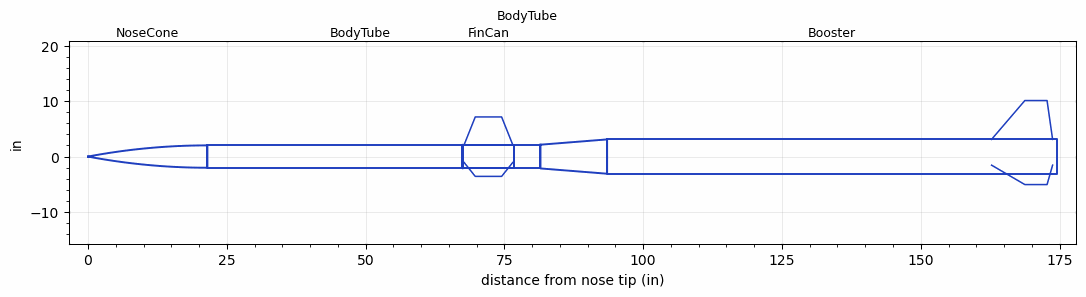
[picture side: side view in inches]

<RASAeroDocument>
 <FileVersion>2</FileVersion>
 <RocketDesign>
  <NoseCone>
   <Length>21.5</Length>
   <Diameter>4.026</Diameter>
   <Shape>Tangent Ogive</Shape>
   <BluntRadius>0.125</BluntRadius>
   <Location>0</Location>
  </NoseCone>
  <BodyTube>
   <Length>55.25</Length>
   <Diameter>4.026</Diameter>
   <Location>21.5</Location>
  </BodyTube>
  <FinCan>
   <Length>9.25</Length>
   <Diameter>4.276</Diameter>
   <InsideDiameter>4.026</InsideDiameter>
   <Location>76.75</Location>
   <ShoulderLength>0.125</ShoulderLength>
   <Offset>-9.25</Offset>
   <Fin>
    <Count>3</Count>
    <Chord>8.75</Chord>
    <Span>5</Span>
    <SweepDistance>2</SweepDistance>
    <TipChord>4.75</TipChord>
    <Thickness>0.125</Thickness>
    <LERadius>0.0625</LERadius>
    <Location>9</Location>
    <AirfoilSection>Hexagonal</AirfoilSection>
    <FX1>0.5</FX1>
    <FX3>0.5</FX3>
   </Fin>
  </FinCan>
  <BodyTube>
   <Length>4.75</Length>
   <Diameter>4.276</Diameter>
   <Location>76.75</Location>
  </BodyTube>
  <Booster>
   <Length>81</Length>
   <Diameter>6.18</Diameter>
   <InsideDiameter>4.276</InsideDiameter>
   <RailGuideDiameter>1.25</RailGuideDiameter>
   <RailGuideHeight>1</RailGuideHeight>
   <Location>81.5</Location>
   <ShoulderLength>12</ShoulderLength>
   <Fin>
    <Count>3</Count>
    <Chord>11</Chord>
    <Span>7</Span>
    <SweepDistance>6</SweepDistance>
    <TipChord>4</TipChord>
    <Thickness>0.125</Thickness>
    <LERadius>0.0625</LERadius>
    <Location>11.75</Location>
    <AirfoilSection>Hexagonal</AirfoilSection>
    <FX1>0.5</FX1>
    <FX3>0.5</FX3>
   </Fin>
  </Booster>
  <Surface>Rough Camouflage Paint</Surface>
  <ModifiedBarrowman>True</ModifiedBarrowman>
  <Turbulence>True</Turbulence>
  <UseBooster1>False</UseBooster1>
  <UseBooster2>False</UseBooster2>
 </RocketDesign>
 <LaunchSite>
  <Altitude>3500</Altitude>
  <Pressure>0</Pressure>
  <RodAngle>1</RodAngle>
  <RodLength>18</RodLength>
  <Temperature>80</Temperature>
  <WindSpeed>2</WindSpeed>
 </LaunchSite>
 <Recovery>
  <Altitude1>1000</Altitude1>
  <Altitude2>1000</Altitude2>
  <DeviceType1>None</DeviceType1>
  <DeviceType2>None</DeviceType2>
  <Event1>False</Event1>
  <Event2>False</Event2>
  <Size1>1</Size1>
  <Size2>1</Size2>
  <EventType1>None</EventType1>
  <EventType2>None</EventType2>
  <CD1>1.33</CD1>
  <CD2>1.33</CD2>
 </Recovery>
 <SimulationList>
  <Simulation>
   <SustainerEngine>K735-SK-P  (CTI)</SustainerEngine>
   <SustainerLaunchWt>26.5</SustainerLaunchWt>
   <SustainerNozzleDiameter>2.75</SustainerNozzleDiameter>
   <SustainerCG>55</SustainerCG>
   <SustainerIgnitionDelay>2</SustainerIgnitionDelay>
   <Booster1Engine>M3400-WT  (CTI)</Booster1Engine>
   <Booster1LaunchWt>83</Booster1LaunchWt>
   <Booster1SeparationDelay>0.5</Booster1SeparationDelay>
   <Booster1IgnitionDelay>0</Booster1IgnitionDelay>
   <Booster1CG>110</Booster1CG>
   <Booster1NozzleDiameter>3.625</Booster1NozzleDiameter>
   <IncludeBooster1>True</IncludeBooster1>
   <Booster2Delay>0</Booster2Delay>
   <IncludeBooster2>True</IncludeBooster2>
   <TimetoApogee>32.35056</TimetoApogee>
   <MaxAltitude>16364.87</MaxAltitude>
   <MaxVelocity>1095.519</MaxVelocity>
  </Simulation>
  <Simulation>
   <SustainerEngine>K735-SK-P  (CTI)</SustainerEngine>
   <SustainerLaunchWt>26.5</SustainerLaunchWt>
   <SustainerNozzleDiameter>2.75</SustainerNozzleDiameter>
   <SustainerCG>55</SustainerCG>
   <SustainerIgnitionDelay>2</SustainerIgnitionDelay>
   <Booster1Engine>M2505  (CTI)</Booster1Engine>
   <Booster1LaunchWt>79</Booster1LaunchWt>
   <Booster1SeparationDelay>0.5</Booster1SeparationDelay>
   <Booster1IgnitionDelay>0</Booster1IgnitionDelay>
   <Booster1CG>108</Booster1CG>
   <Booster1NozzleDiameter>3.625</Booster1NozzleDiameter>
   <IncludeBooster1>True</IncludeBooster1>
   <Booster2Delay>0</Booster2Delay>
   <IncludeBooster2>False</IncludeBooster2>
   <TimetoApogee>30.52052</TimetoApogee>
   <MaxAltitude>13441.91</MaxAltitude>
   <MaxVelocity>960.9597</MaxVelocity>
  </Simulation>
  <Simulation>
   <SustainerEngine>K510  (CTI)</SustainerEngine>
   <SustainerLaunchWt>26.5</SustainerLaunchWt>
   <SustainerNozzleDiameter>2.75</SustainerNozzleDiameter>
   <SustainerCG>55</SustainerCG>
   <SustainerIgnitionDelay>2</SustainerIgnitionDelay>
   <Booster1Engine>M2505  (CTI)</Booster1Engine>
   <Booster1LaunchWt>79</Booster1LaunchWt>
   <Booster1SeparationDelay>0.5</Booster1SeparationDelay>
   <Booster1IgnitionDelay>0</Booster1IgnitionDelay>
   <Booster1CG>108</Booster1CG>
   <Booster1NozzleDiameter>3.625</Booster1NozzleDiameter>
   <IncludeBooster1>True</IncludeBooster1>
   <Booster2Delay>0</Booster2Delay>
   <IncludeBooster2>False</IncludeBooster2>
   <TimetoApogee>33.8906</TimetoApogee>
   <MaxAltitude>16404.34</MaxAltitude>
   <MaxVelocity>1028.177</MaxVelocity>
  </Simulation>
  <Simulation>
   <SustainerEngine>K510  (CTI)</SustainerEngine>
   <SustainerLaunchWt>26.5</SustainerLaunchWt>
   <SustainerNozzleDiameter>2.75</SustainerNozzleDiameter>
   <SustainerCG>55</SustainerCG>
   <SustainerIgnitionDelay>2</SustainerIgnitionDelay>
   <Booster1Engine>M3400-WT  (CTI)</Booster1Engine>
   <Booster1LaunchWt>83</Booster1LaunchWt>
   <Booster1SeparationDelay>0.5</Booster1SeparationDelay>
   <Booster1IgnitionDelay>0</Booster1IgnitionDelay>
   <Booster1CG>110</Booster1CG>
   <Booster1NozzleDiameter>3.625</Booster1NozzleDiameter>
   <IncludeBooster1>True</IncludeBooster1>
   <Booster2Delay>0</Booster2Delay>
   <IncludeBooster2>False</IncludeBooster2>
   <TimetoApogee>34.99062</TimetoApogee>
   <MaxAltitude>18911.57</MaxAltitude>
   <MaxVelocity>1112.528</MaxVelocity>
  </Simulation>
  <Simulation>
   <SustainerEngine>K510  (CTI)</SustainerEngine>
   <SustainerLaunchWt>26.5</SustainerLaunchWt>
   <SustainerNozzleDiameter>2.75</SustainerNozzleDiameter>
   <SustainerCG>55</SustainerCG>
   <SustainerIgnitionDelay>2</SustainerIgnitionDelay>
   <Booster1Engine>M2075-SS  (CTI)</Booster1Engine>
   <Booster1LaunchWt>81</Booster1LaunchWt>
   <Booster1SeparationDelay>0.5</Booster1SeparationDelay>
   <Booster1IgnitionDelay>0</Booster1IgnitionDelay>
   <Booster1CG>107</Booster1CG>
   <Booster1NozzleDiameter>3.625</Booster1NozzleDiameter>
   <IncludeBooster1>True</IncludeBooster1>
   <Booster2Delay>0</Booster2Delay>
   <IncludeBooster2>False</IncludeBooster2>
   <TimetoApogee>32.75057</TimetoApogee>
   <MaxAltitude>14598.02</MaxAltitude>
   <MaxVelocity>954.5581</MaxVelocity>
  </Simulation>
 </SimulationList>
</RASAeroDocument>
